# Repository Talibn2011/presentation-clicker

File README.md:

# presentation-clicker
arm to click button

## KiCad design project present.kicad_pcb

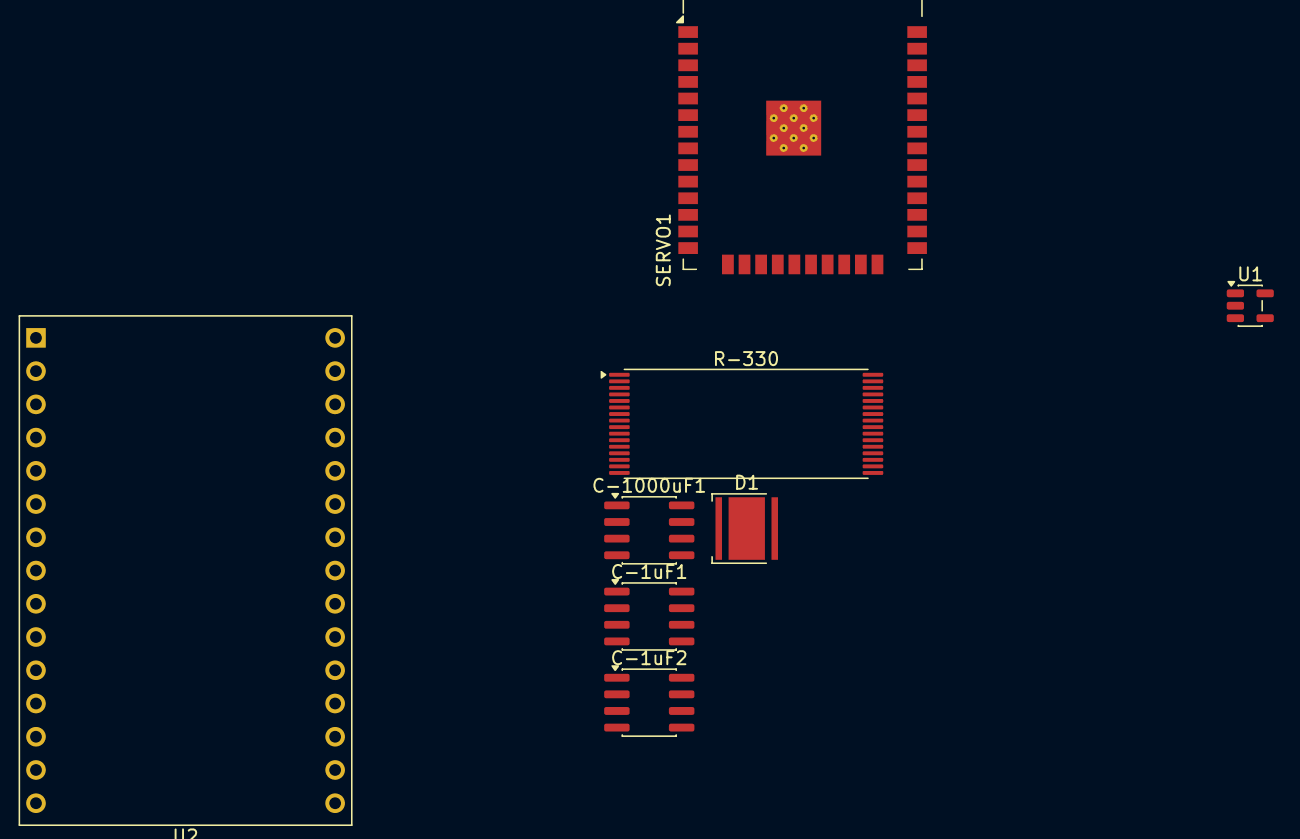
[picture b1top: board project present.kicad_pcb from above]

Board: 2 copper layers, 8 parts (0 on the bottom side), 8 nets, no tracks yet.

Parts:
C-1uF1, C-1uF2: C_Polarized_Small; SOIC-8_3.9x4.9mm_P1.27mm
C-1000uF1: C_Polarized; SOIC-8_3.9x4.9mm_P1.27mm
D1: LED; LED_Cree-XHP50_3V_HighDensity
R-330: R_Small; TSOP-I-32_18.4x8mm_P0.5mm
SERVO1: Conn_01x03; ESP32-WROOM-32
U1: AP2112K-3.3; SOT-23-5
U2: ESP32-C3-DevKitM-1

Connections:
3.3V: C-1uF1.1, U2.2 (3V3), U2.3 (3V3)
5V: C-1uF2.1, C-1000uF1.1, SERVO1.1, U1.1 (VIN), U1.3 (EN)
GND: C-1uF2.2, C-1000uF1.2, D1.2 (A), SERVO1.3, U1.2 (GND), U2.1 (GND), U2.6 (GND), U2.8 (GND), U2.12 (GND), U2.15 (GND), U2.16 (GND), U2.19 (GND), U2.24 (GND), U2.27 (GND), U2.30 (GND)
unnamed: D1.1 (K), R-330.2
unnamed: SERVO1.2, U2.20 (IO4)
unnamed: C-1uF1.2, U1.5 (VOUT)
unnamed: U2.13 (5V), U2.14 (5V)
unnamed: R-330.1, U2.23 (IO7)
